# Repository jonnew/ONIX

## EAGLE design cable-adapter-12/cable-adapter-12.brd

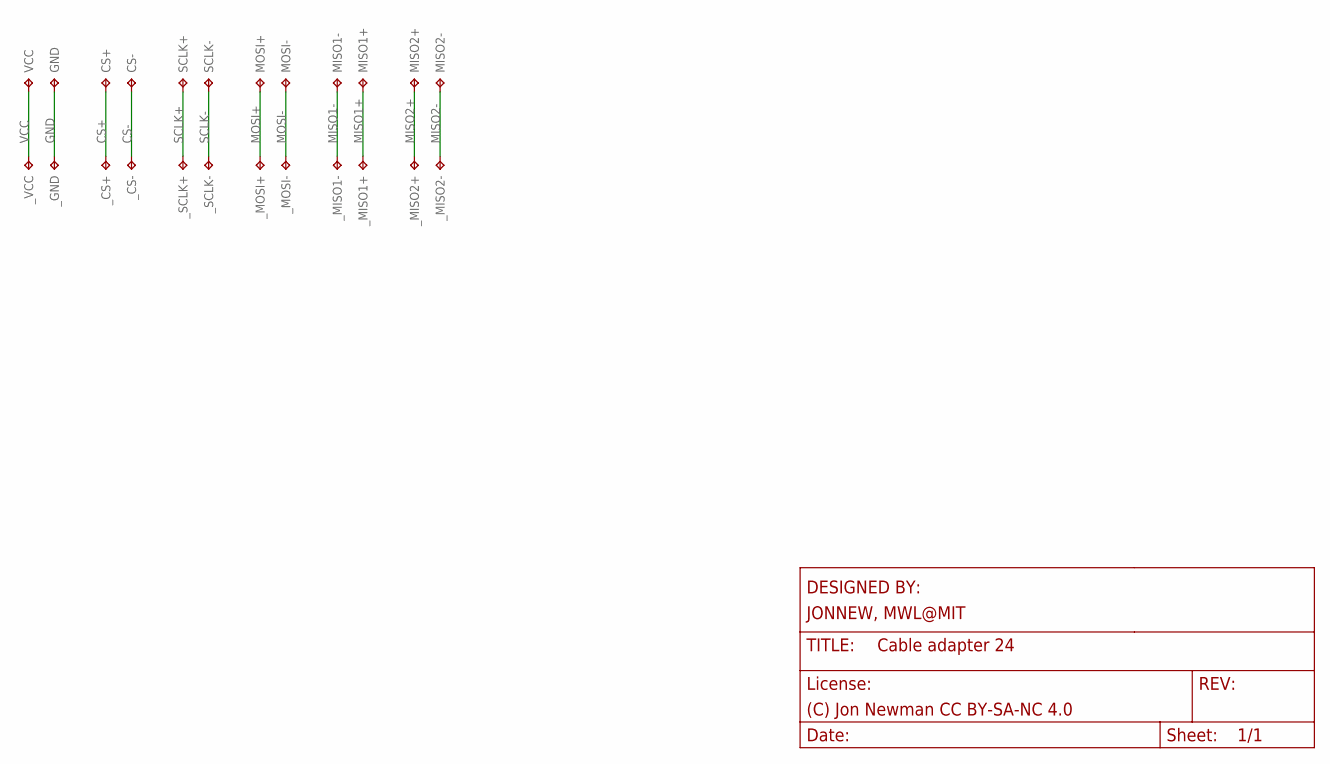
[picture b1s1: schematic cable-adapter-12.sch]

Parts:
CS+: TP_SPI_WIRE+; SPI_WIRE+
CS-: TP_SPI_WIRE+; SPI_WIRE+
GND: TP_SPI_WIRE+; SPI_WIRE+
MISO1+, MISO1-, MISO2+, MISO2-: TP_SPI_WIRE+; SPI_WIRE+
MOSI+: TP_SPI_WIRE+; SPI_WIRE+
MOSI-: TP_SPI_WIRE+; SPI_WIRE+
SCLK+: TP_SPI_WIRE+; SPI_WIRE+
SCLK-: TP_SPI_WIRE+; SPI_WIRE+
VCC: TP_SPI_WIRE+; SPI_WIRE+
_CS+: TP_SPI_WIRE+; SPI_WIRE+
_CS-: TP_SPI_WIRE+; SPI_WIRE+
_GND: TP_SPI_WIRE+; SPI_WIRE+
_MISO1+, _MISO1-, _MISO2+, _MISO2-: TP_SPI_WIRE+; SPI_WIRE+
_MOSI+: TP_SPI_WIRE+; SPI_WIRE+
_MOSI-: TP_SPI_WIRE+; SPI_WIRE+
_SCLK+: TP_SPI_WIRE+; SPI_WIRE+
_SCLK-: TP_SPI_WIRE+; SPI_WIRE+
_VCC: TP_SPI_WIRE+; SPI_WIRE+

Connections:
CS+: CS+.P$1, _CS+.P$1
CS-: CS-.P$1, _CS-.P$1
GND: GND.P$1, _GND.P$1
MISO1+: MISO1+.P$1, _MISO1+.P$1
MISO1-: MISO1-.P$1, _MISO1-.P$1
MISO2+: MISO2+.P$1, _MISO2+.P$1
MISO2-: MISO2-.P$1, _MISO2-.P$1
MOSI+: MOSI+.P$1, _MOSI+.P$1
MOSI-: MOSI-.P$1, _MOSI-.P$1
SCLK+: SCLK+.P$1, _SCLK+.P$1
SCLK-: SCLK-.P$1, _SCLK-.P$1
VCC: VCC.P$1, _VCC.P$1

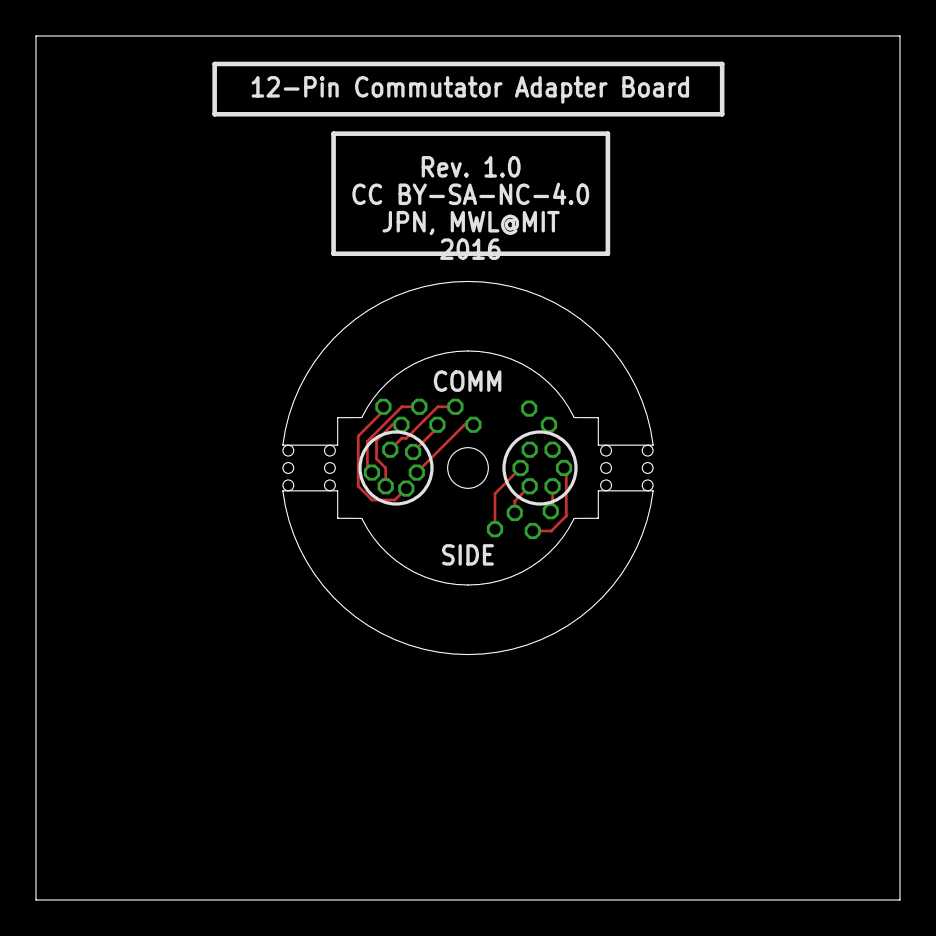
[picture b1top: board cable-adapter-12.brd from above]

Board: 4 copper layers, 48.0 x 48.0 mm, 24 parts (0 on the bottom side), 12 nets.

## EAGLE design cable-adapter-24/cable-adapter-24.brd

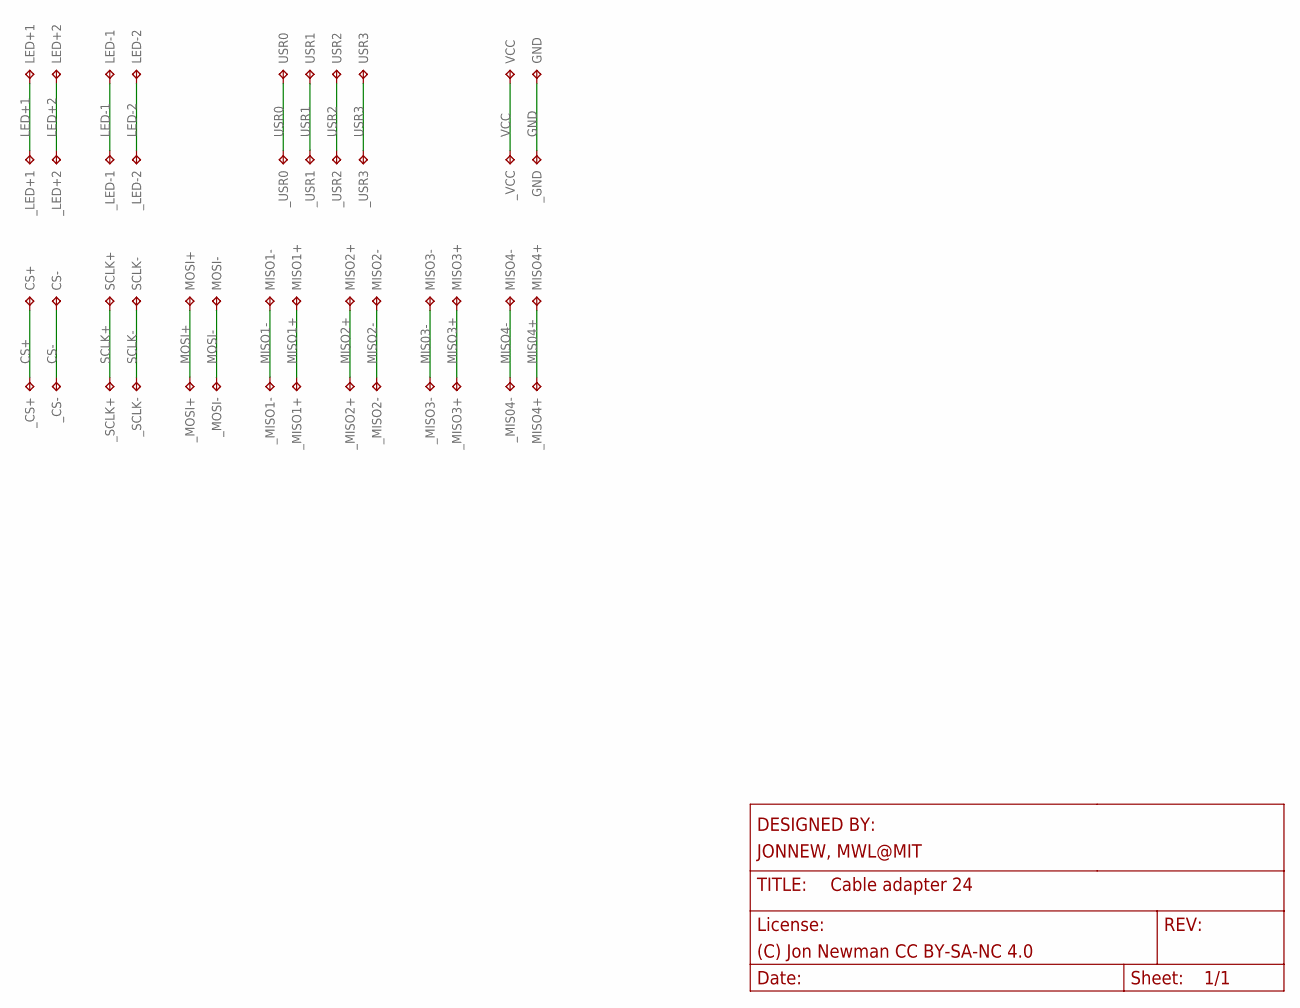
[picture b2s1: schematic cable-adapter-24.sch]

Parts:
CS+: TP_SPI_WIRE+; SPI_WIRE+
CS-: TP_SPI_WIRE+; SPI_WIRE+
GND: TP_SPI_WIRE+; SPI_WIRE+
LED+1, LED+2: TP_SPI_WIRE+; SPI_WIRE+
LED-1, LED-2: TP_SPI_WIRE+; SPI_WIRE+
MISO1+, MISO1-, MISO2+, MISO2-, MISO3+, MISO3-, MISO4+, MISO4-: TP_SPI_WIRE+; SPI_WIRE+
MOSI+: TP_SPI_WIRE+; SPI_WIRE+
MOSI-: TP_SPI_WIRE+; SPI_WIRE+
SCLK+: TP_SPI_WIRE+; SPI_WIRE+
SCLK-: TP_SPI_WIRE+; SPI_WIRE+
USR0, USR1, USR2, USR3: TP_SPI_WIRE+; SPI_WIRE+
VCC: TP_SPI_WIRE+; SPI_WIRE+
_CS+: TP_SPI_WIRE+; SPI_WIRE+
_CS-: TP_SPI_WIRE+; SPI_WIRE+
_GND: TP_SPI_WIRE+; SPI_WIRE+
_LED+1, _LED+2: TP_SPI_WIRE+; SPI_WIRE+
_LED-1, _LED-2: TP_SPI_WIRE+; SPI_WIRE+
_MIS04-: TP_SPI_WIRE+; SPI_WIRE+
_MISO1+, _MISO1-, _MISO2+, _MISO2-, _MISO3+, _MISO3-: TP_SPI_WIRE+; SPI_WIRE+
_MISO4+: MISO3+; SPI_WIRE+
_MOSI+: TP_SPI_WIRE+; SPI_WIRE+
_MOSI-: TP_SPI_WIRE+; SPI_WIRE+
_SCLK+: TP_SPI_WIRE+; SPI_WIRE+
_SCLK-: TP_SPI_WIRE+; SPI_WIRE+
_USR0, _USR1, _USR2, _USR3: TP_SPI_WIRE+; SPI_WIRE+
_VCC: TP_SPI_WIRE+; SPI_WIRE+

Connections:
CS+: CS+.P$1, _CS+.P$1
CS-: CS-.P$1, _CS-.P$1
GND: GND.P$1, _GND.P$1
LED+1: LED+1.P$1, _LED+1.P$1
LED+2: LED+2.P$1, _LED+2.P$1
LED-1: LED-1.P$1, _LED-1.P$1
LED-2: LED-2.P$1, _LED-2.P$1
MIS03-: MISO3-.P$1, _MISO3-.P$1
MIS04+: MISO4+.P$1, _MISO4+.P$1
MISO1+: MISO1+.P$1, _MISO1+.P$1
MISO1-: MISO1-.P$1, _MISO1-.P$1
MISO2+: MISO2+.P$1, _MISO2+.P$1
MISO2-: MISO2-.P$1, _MISO2-.P$1
MISO3+: MISO3+.P$1, _MISO3+.P$1
MISO4-: MISO4-.P$1, _MIS04-.P$1
MOSI+: MOSI+.P$1, _MOSI+.P$1
MOSI-: MOSI-.P$1, _MOSI-.P$1
SCLK+: SCLK+.P$1, _SCLK+.P$1
SCLK-: SCLK-.P$1, _SCLK-.P$1
USR0: USR0.P$1, _USR0.P$1
USR1: USR1.P$1, _USR1.P$1
USR2: USR2.P$1, _USR2.P$1
USR3: USR3.P$1, _USR3.P$1
VCC: VCC.P$1, _VCC.P$1

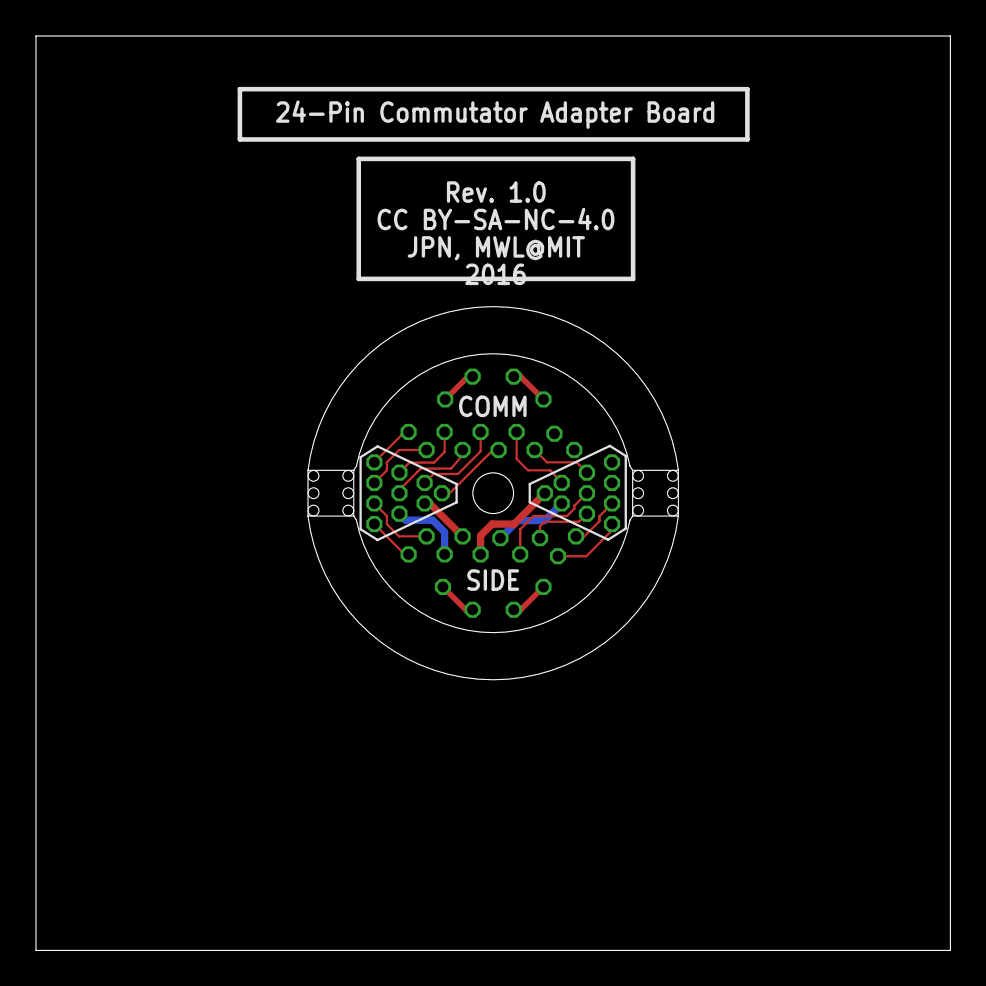
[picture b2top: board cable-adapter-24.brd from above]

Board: 4 copper layers, 50.8 x 50.8 mm, 48 parts (0 on the bottom side), 24 nets.

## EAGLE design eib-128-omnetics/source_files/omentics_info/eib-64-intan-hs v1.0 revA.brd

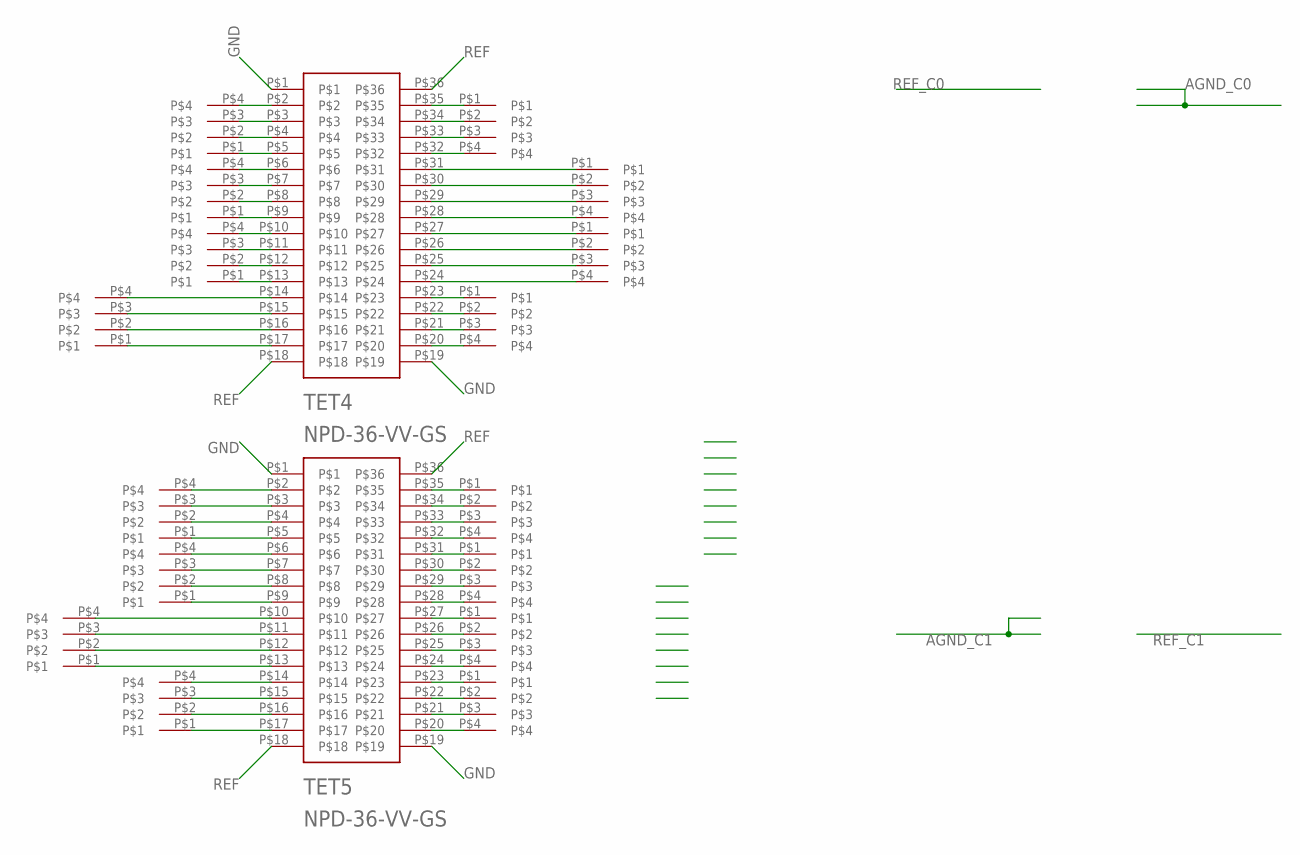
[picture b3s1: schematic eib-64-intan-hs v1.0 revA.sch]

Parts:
TET0: 0; TET32
TET1: 1; TET32
TET2: 2; TET32
TET3: 3; TET32
TET4, TET5: NPD-36-VV-GS
TET8: 8; TET32
TET9: 9; TET32
TET10: 10; TET32
TET11: 11; TET32
TET12: 12; TET32
TET13: 13; TET32
TET14: 14; TET32
TET15: 15; TET32
TET20: 20; TET32
TET21: 21; TET32
TET22: 22; TET32
TET23: 23; TET32

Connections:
GND: TET4.P$1, TET4.P$19, TET5.P$1, TET5.P$19
unnamed: TET5.P$6, TET9.P$4
unnamed: TET5.P$2, TET8.P$4
unnamed: TET5.P$3, TET8.P$3
unnamed: TET5.P$4, TET8.P$2
unnamed: TET5.P$5, TET8.P$1
unnamed: TET5.P$7, TET9.P$3
unnamed: TET5.P$8, TET9.P$2
unnamed: TET5.P$9, TET9.P$1
unnamed: TET5.P$10, TET14.P$4
unnamed: TET5.P$11, TET14.P$3
unnamed: TET5.P$28, TET11.P$4
unnamed: TET5.P$27, TET12.P$1
unnamed: TET5.P$26, TET12.P$2
unnamed: TET5.P$25, TET12.P$3
unnamed: TET5.P$24, TET12.P$4
unnamed: TET5.P$23, TET13.P$1
unnamed: TET5.P$22, TET13.P$2
unnamed: TET5.P$21, TET13.P$3
unnamed: TET5.P$35, TET10.P$1
unnamed: TET5.P$34, TET10.P$2
unnamed: TET5.P$33, TET10.P$3
unnamed: TET5.P$32, TET10.P$4
unnamed: TET5.P$31, TET11.P$1
unnamed: TET5.P$30, TET11.P$2
unnamed: TET5.P$29, TET11.P$3
unnamed: TET5.P$12, TET14.P$2
unnamed: TET5.P$13, TET14.P$1
unnamed: TET5.P$14, TET15.P$4
unnamed: TET5.P$15, TET15.P$3
unnamed: TET5.P$16, TET15.P$2
unnamed: TET5.P$17, TET15.P$1
unnamed: TET1.P$4, TET4.P$2
unnamed: TET1.P$3, TET4.P$3
unnamed: TET1.P$2, TET4.P$4
unnamed: TET1.P$1, TET4.P$5
unnamed: TET0.P$4, TET4.P$6
unnamed: TET0.P$3, TET4.P$7
unnamed: TET0.P$2, TET4.P$8
unnamed: TET0.P$1, TET4.P$9
unnamed: TET3.P$1, TET4.P$35
unnamed: TET3.P$2, TET4.P$34
unnamed: TET3.P$3, TET4.P$33
unnamed: TET3.P$4, TET4.P$32
unnamed: TET2.P$1, TET4.P$31
unnamed: TET2.P$2, TET4.P$30
unnamed: TET5.P$20, TET13.P$4
unnamed: TET2.P$4, TET4.P$28
unnamed: TET4.P$27, TET21.P$1
unnamed: TET4.P$25, TET21.P$3
unnamed: TET4.P$26, TET21.P$2
unnamed: TET4.P$24, TET21.P$4
unnamed: TET4.P$23, TET20.P$1
unnamed: TET4.P$22, TET20.P$2
unnamed: TET4.P$21, TET20.P$3
unnamed: TET4.P$20, TET20.P$4
unnamed: TET4.P$10, TET23.P$4
unnamed: TET4.P$11, TET23.P$3
unnamed: TET4.P$12, TET23.P$2
unnamed: TET4.P$13, TET23.P$1
unnamed: TET4.P$14, TET22.P$4
unnamed: TET4.P$15, TET22.P$3
unnamed: TET4.P$16, TET22.P$2
unnamed: TET4.P$17, TET22.P$1
unnamed: TET2.P$3, TET4.P$29
REF: TET4.P$18, TET4.P$36, TET5.P$18, TET5.P$36

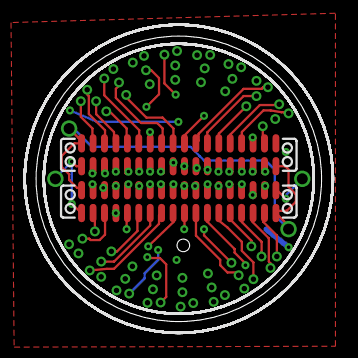
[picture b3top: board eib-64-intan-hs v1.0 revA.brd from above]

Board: 4 copper layers, 15.9 x 15.9 mm, 18 parts (0 on the bottom side), 66 nets.

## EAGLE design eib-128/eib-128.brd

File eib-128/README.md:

# eib-128
128-channel electrode interface board (EIB) with electrical and optical
stimulation. Designed for large animal (e.g. rat) tetrode electrophysiology.
Compatible with [headstage-256](../headstage-256/) and large shuttle-drives.

## Gerber Files
{% include gerber_layers.md %}

## Bill of Materials
The BOM is located on [this google
sheet](https://docs.google.com/spreadsheets/d/1F-KWcdvH_63iXjZf0cgCfDiFX6XXW3qw6rlR8DZrFpQ/edit#gid=1129179247).

## Pinout
The EIB pinout (ADC input mapping, stimulation connections, etc) is located on
[this google
sheet](https://docs.google.com/spreadsheets/d/11wRDYOqHN5lPb03yUdfXfK0zvaDYsVetplaNK-R90Gg/edit#gid=663991061)

## Tetrode Connectorization
This EIB uses Neuralynx ["large" gold pins](https://neuralynx.com/hardware/large-eib-pins) to attach tetrode wires. Usage instructions are provided in the [Neuralynx EIB pin Manual](https://neuralynx.com/documents/EIB%20Pins%20Manual.pdf).

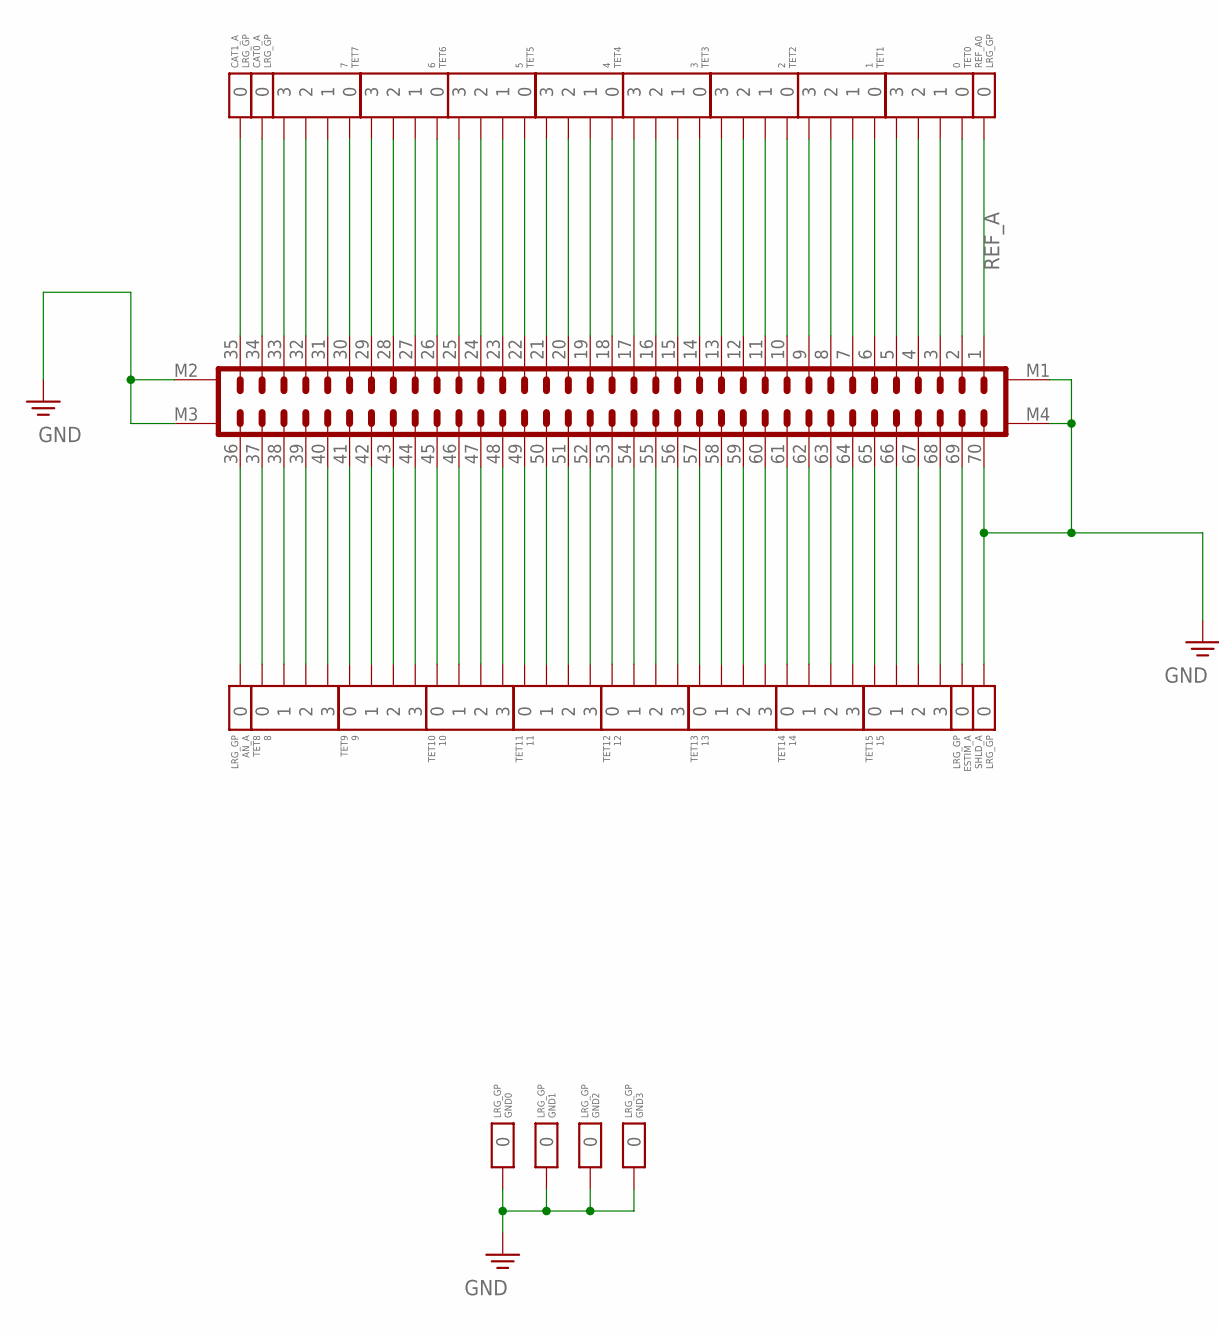
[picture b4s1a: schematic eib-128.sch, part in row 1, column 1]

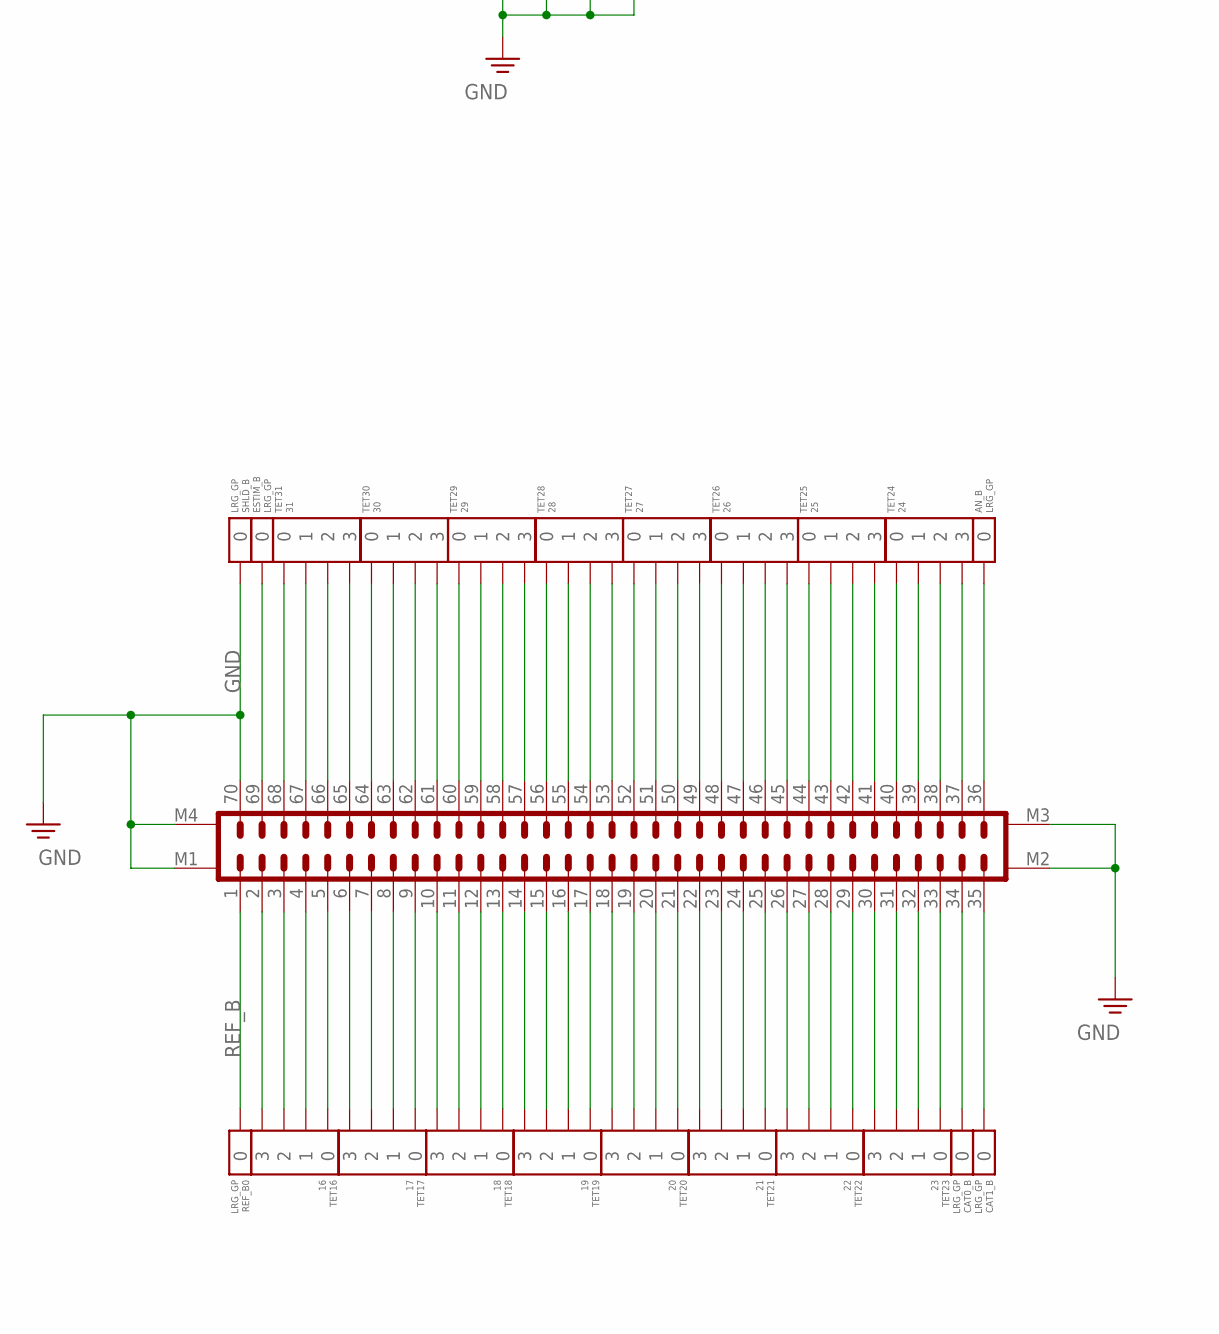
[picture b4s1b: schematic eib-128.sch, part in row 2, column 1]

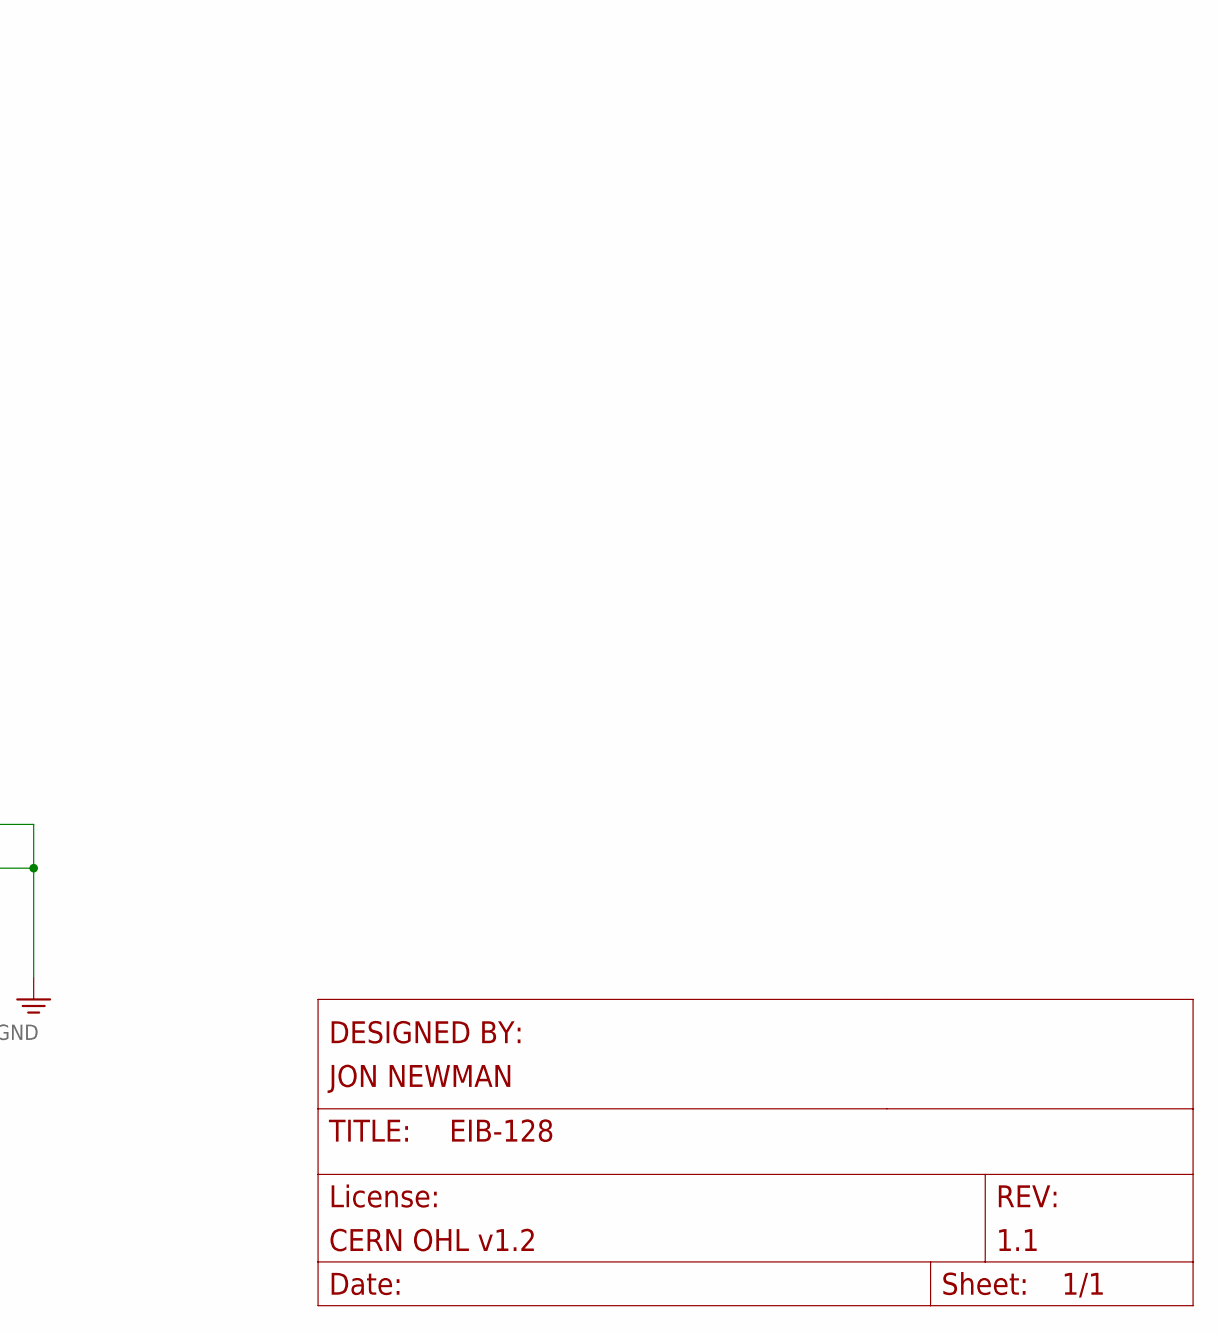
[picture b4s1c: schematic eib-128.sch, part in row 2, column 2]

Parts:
A: DF40HEAD; DF40-70HEAD
AN_A: LRG_GP; GOLDPIN_0.5ID_0.7OD
AN_B: LRG_GP; GOLDPIN_0.5ID_0.7OD
B: DF40HEAD; DF40-70HEAD
CAT0_A, CAT0_B, CAT1_A, CAT1_B: LRG_GP; GOLDPIN_0.5ID_0.7OD
ESTIM_A: LRG_GP; GOLDPIN_0.5ID_0.7OD
ESTIM_B: LRG_GP; GOLDPIN_0.5ID_0.7OD
GND0, GND1, GND2, GND3: LRG_GP; GOLDPIN_0.5ID_0.7OD
REF_A0: LRG_GP; GOLDPIN_0.5ID_0.7OD
REF_B0: LRG_GP; GOLDPIN_0.5ID_0.7OD
SHLD_A: LRG_GP; GOLDPIN_0.5ID_0.7OD
SHLD_B: LRG_GP; GOLDPIN_0.5ID_0.7OD
TET0: 0; TETRODE_128_0.5ID_0.7OD
TET1: 1; TETRODE_128_0.5ID_0.7OD
TET2: 2; TETRODE_128_0.5ID_0.7OD
TET3: 3; TETRODE_128_0.5ID_0.7OD
TET4: 4; TETRODE_128_0.5ID_0.7OD
TET5: 5; TETRODE_128_0.5ID_0.7OD
TET6: 6; TETRODE_128_0.5ID_0.7OD
TET7: 7; TETRODE_128_0.5ID_0.7OD
TET8: 8; TETRODE_128_0.5ID_0.7OD
TET9: 9; TETRODE_128_0.5ID_0.7OD
TET10: 10; TETRODE_128_0.5ID_0.7OD
TET11: 11; TETRODE_128_0.5ID_0.7OD
TET12: 12; TETRODE_128_0.5ID_0.7OD
TET13: 13; TETRODE_128_0.5ID_0.7OD
TET14: 14; TETRODE_128_0.5ID_0.7OD
TET15: 15; TETRODE_128_0.5ID_0.7OD
TET16: 16; TETRODE_128_0.5ID_0.7OD
TET17: 17; TETRODE_128_0.5ID_0.7OD
TET18: 18; TETRODE_128_0.5ID_0.7OD
TET19: 19; TETRODE_128_0.5ID_0.7OD
TET20: 20; TETRODE_128_0.5ID_0.7OD
TET21: 21; TETRODE_128_0.5ID_0.7OD
TET22: 22; TETRODE_128_0.5ID_0.7OD
TET23: 23; TETRODE_128_0.5ID_0.7OD
TET24: 24; TETRODE_128_0.5ID_0.7OD
TET25: 25; TETRODE_128_0.5ID_0.7OD
TET26: 26; TETRODE_128_0.5ID_0.7OD
TET27: 27; TETRODE_128_0.5ID_0.7OD
TET28: 28; TETRODE_128_0.5ID_0.7OD
TET29: 29; TETRODE_128_0.5ID_0.7OD
TET30: 30; TETRODE_128_0.5ID_0.7OD
TET31: 31; TETRODE_128_0.5ID_0.7OD

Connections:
AN_A: A.36, AN_A.P$1
AN_B: AN_B.P$1, B.36
CAT0_A: A.34, CAT0_A.P$1
CAT0_B: B.34, CAT0_B.P$1
CAT1_A: A.35, CAT1_A.P$1
CAT1_B: B.35, CAT1_B.P$1
ESTIM_A: A.69, ESTIM_A.P$1
ESTIM_B: B.69, ESTIM_B.P$1
GND: A.70, A.M1, A.M2, A.M3, A.M4, B.70, B.M1, B.M2, B.M3, B.M4, GND0.P$1, GND1.P$1, GND2.P$1, GND3.P$1, SHLD_A.P$1, SHLD_B.P$1
unnamed: B.33, TET23.0
unnamed: B.32, TET23.1
unnamed: B.31, TET23.2
unnamed: B.30, TET23.3
unnamed: B.29, TET22.0
unnamed: B.28, TET22.1
unnamed: B.27, TET22.2
unnamed: B.26, TET22.3
unnamed: B.25, TET21.0
unnamed: B.24, TET21.1
unnamed: B.23, TET21.2
unnamed: B.22, TET21.3
unnamed: B.21, TET20.0
unnamed: B.20, TET20.1
unnamed: B.19, TET20.2
unnamed: B.18, TET20.3
unnamed: B.17, TET19.0
unnamed: B.16, TET19.1
unnamed: B.15, TET19.2
unnamed: B.14, TET19.3
unnamed: B.13, TET18.0
unnamed: B.12, TET18.1
unnamed: B.11, TET18.2
unnamed: B.10, TET18.3
unnamed: B.9, TET17.0
unnamed: B.8, TET17.1
unnamed: B.7, TET17.2
unnamed: B.6, TET17.3
unnamed: B.5, TET16.0
unnamed: B.4, TET16.1
unnamed: B.3, TET16.2
unnamed: B.38, TET24.2
unnamed: B.39, TET24.1
unnamed: B.40, TET24.0
unnamed: B.41, TET25.3
unnamed: B.42, TET25.2
unnamed: B.43, TET25.1
unnamed: B.44, TET25.0
unnamed: B.45, TET26.3
unnamed: B.46, TET26.2
unnamed: B.47, TET26.1
unnamed: B.48, TET26.0
unnamed: B.49, TET27.3
unnamed: B.50, TET27.2
unnamed: B.51, TET27.1
unnamed: B.52, TET27.0
unnamed: B.53, TET28.3
unnamed: B.54, TET28.2
unnamed: B.55, TET28.1
unnamed: B.56, TET28.0
unnamed: B.57, TET29.3
unnamed: B.58, TET29.2
unnamed: B.59, TET29.1
unnamed: B.60, TET29.0
unnamed: B.61, TET30.3
unnamed: B.62, TET30.2
unnamed: B.63, TET30.1
unnamed: B.64, TET30.0
unnamed: B.65, TET31.3
unnamed: B.66, TET31.2
unnamed: B.67, TET31.1
unnamed: B.68, TET31.0
unnamed: B.2, TET16.3
unnamed: B.37, TET24.3
unnamed: A.33, TET7.3
unnamed: A.32, TET7.2
unnamed: A.31, TET7.1
unnamed: A.30, TET7.0
unnamed: A.29, TET6.3
unnamed: A.28, TET6.2
unnamed: A.27, TET6.1
unnamed: A.26, TET6.0
unnamed: A.25, TET5.3
unnamed: A.24, TET5.2
unnamed: A.23, TET5.1
unnamed: A.22, TET5.0
unnamed: A.21, TET4.3
unnamed: A.20, TET4.2
unnamed: A.19, TET4.1
unnamed: A.18, TET4.0
unnamed: A.17, TET3.3
unnamed: A.16, TET3.2
unnamed: A.15, TET3.1
unnamed: A.14, TET3.0
unnamed: A.13, TET2.3
unnamed: A.12, TET2.2
unnamed: A.11, TET2.1
unnamed: A.10, TET2.0
unnamed: A.9, TET1.3
unnamed: A.8, TET1.2
unnamed: A.7, TET1.1
unnamed: A.6, TET1.0
unnamed: A.5, TET0.3
unnamed: A.4, TET0.2
unnamed: A.3, TET0.1
unnamed: A.2, TET0.0
unnamed: A.38, TET8.1
unnamed: A.39, TET8.2
unnamed: A.40, TET8.3
unnamed: A.41, TET9.0
unnamed: A.42, TET9.1
unnamed: A.43, TET9.2
unnamed: A.44, TET9.3
unnamed: A.45, TET10.0
unnamed: A.46, TET10.1
unnamed: A.47, TET10.2
unnamed: A.48, TET10.3
unnamed: A.49, TET11.0
unnamed: A.50, TET11.1
unnamed: A.51, TET11.2
unnamed: A.52, TET11.3
unnamed: A.53, TET12.0
unnamed: A.54, TET12.1
unnamed: A.55, TET12.2
unnamed: A.56, TET12.3
unnamed: A.57, TET13.0
unnamed: A.58, TET13.1
unnamed: A.59, TET13.2
unnamed: A.60, TET13.3
unnamed: A.61, TET14.0
unnamed: A.62, TET14.1
unnamed: A.63, TET14.2
unnamed: A.64, TET14.3
unnamed: A.65, TET15.0
unnamed: A.66, TET15.1
unnamed: A.67, TET15.2
unnamed: A.68, TET15.3
unnamed: A.37, TET8.0
REF_A: A.1, REF_A0.P$1
REF_B: B.1, REF_B0.P$1

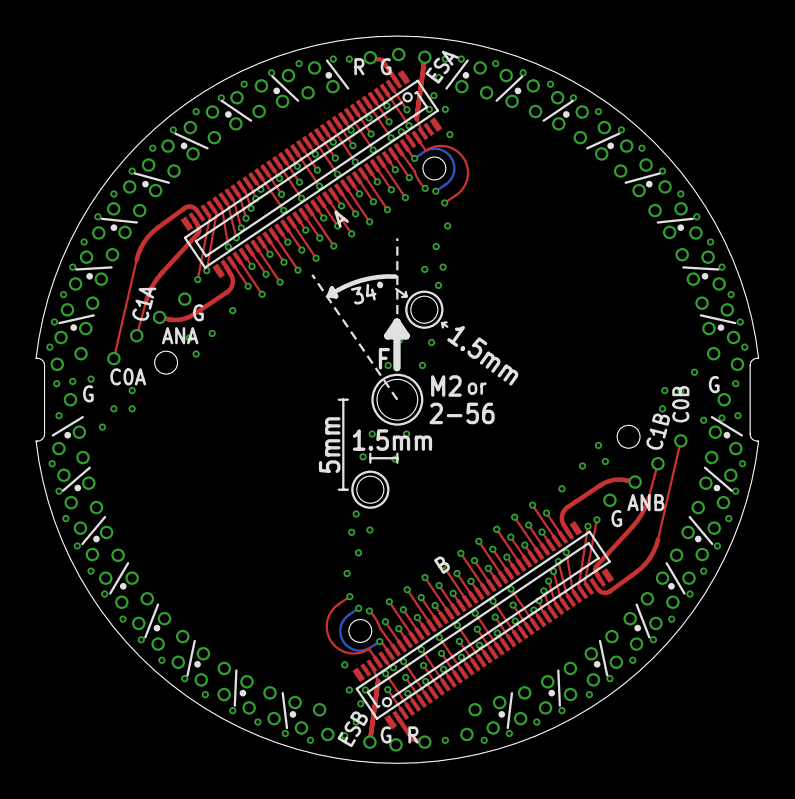
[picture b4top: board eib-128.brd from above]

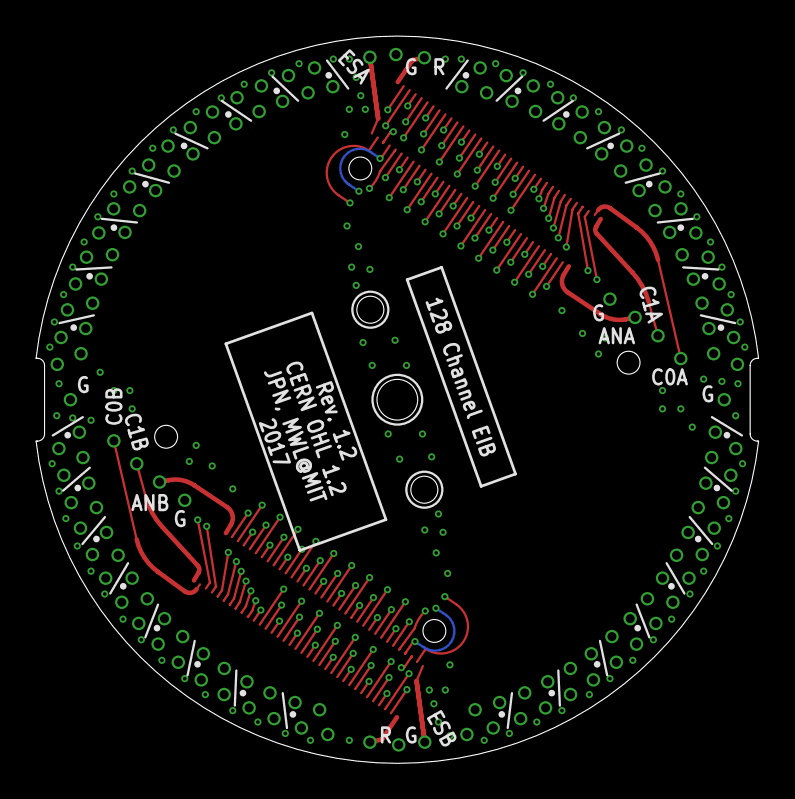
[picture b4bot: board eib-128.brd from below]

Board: 4 copper layers, 40.1 x 40.4 mm, 51 parts (16 on the bottom side), 139 nets.

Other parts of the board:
U$1: EIB_MOUNT_A

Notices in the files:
cable-adapter-12/cable-adapter-12.brd:
CC BY-SA-NC-4.0
cable-adapter-12/cable-adapter-12.sch:
LICENSE: (C) Jon Newman CC BY-SA-NC 4.0
eib-128-omnetics/source_files/omentics_info/eib-64-intan-hs v1.0 revA.sch:
LICENSE: CERN OHL v1.2
eib-128/eib-128.brd:
CERN OHL 1.2
eib-256/eib-256.brd:
CERN OHL v1.2
